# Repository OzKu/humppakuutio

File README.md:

# Humppakuutio - the experience
This is git for our awesome project!

## Parts
- BlueGiga WT32-i (A2DP audiomodule)
- Arduino xyz
- Touchscreen with or without mSD shield
- Opamps for differential audio
- D-Class amplifier
	- Lepai LP-2020A+
- 6x9" car elements
- Some battery
	- LiPo?
	- Lead-acid(12V 7.2Ah)?
	- NiMh?
- Case

## Resources/links

## Idea behind intromenuetc
So I started making introscreen that shows when device is powered up, but nothing is playing.
When it gets streaming is started, it changes to playmenu (own function now).
When phone is disconnected, it changes back to introscreen.

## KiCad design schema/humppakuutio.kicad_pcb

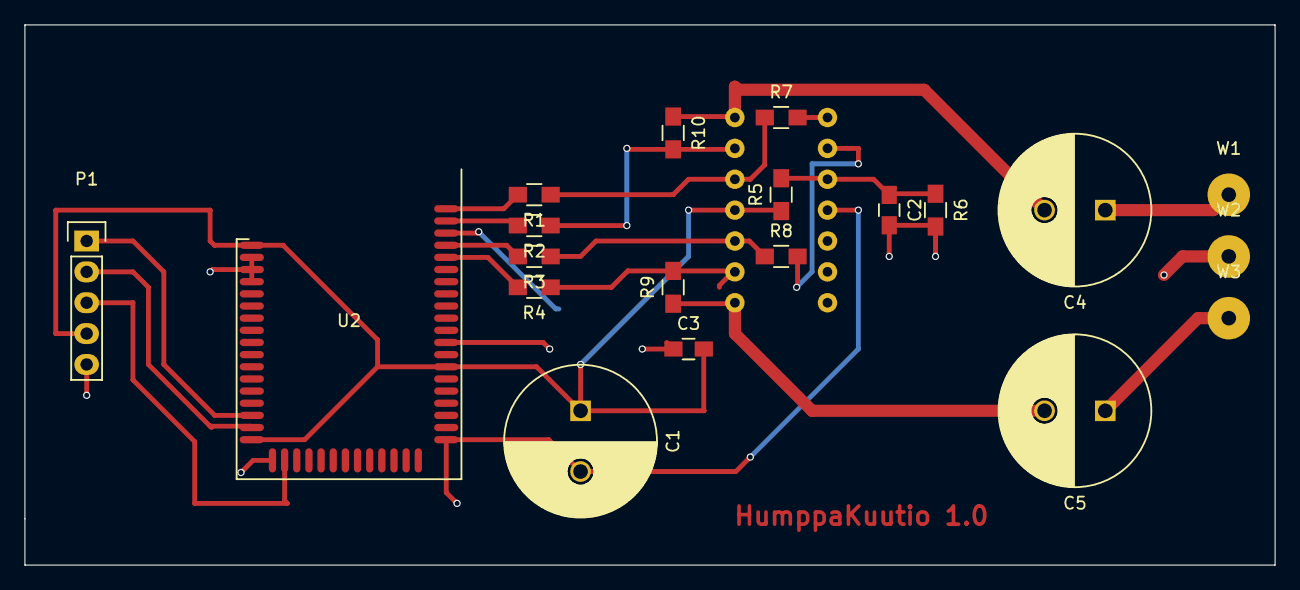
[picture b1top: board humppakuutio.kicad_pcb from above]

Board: 2 copper layers, 102.9 x 44.4 mm, 21 parts (1 on the bottom side), 20 nets.

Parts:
C1, C4, C5: 470u; C_Radial_D12.5_L25_P5
C2, C3: 2u2; C_0805_HandSoldering
P1: CONN_01X05; Pin_Header_Straight_1x05
R1, R2, R3, R4, R5, R6, R7, R8, R9, R10: 10k 0.1%; R_0805_HandSoldering
U1: TL074; DIP-14_W7.62mm
U2: WT32
W1: LEFT; SolderWirePad_single_1-2mmDrill
W2: GNDA; SolderWirePad_single_1-2mmDrill
W3: RIGHT; SolderWirePad_single_1-2mmDrill

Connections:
GNDA: C2.2, C3.1, R6.2, U2.39, U2.43, U2.48, W2.1
GNDD: C1.2, P1.5, U1.11, U2.2, U2.3, U2.4, U2.18, U2.31
unnamed: C2.1, R5.2, R6.1, U1.10
unnamed: C4.1, W1.1
unnamed: C4.2, R10.1, U1.7
unnamed: C5.1, W3.1
unnamed: C5.2, R9.1, U1.1
unnamed: P1.1, U2.15
unnamed: P1.2, U2.16
unnamed: P1.3, U2.19
unnamed: R1.1, R7.1, U1.5
unnamed: R1.2, U2.50
unnamed: R2.2, U2.49
unnamed: R3.1, R8.1, U1.3
unnamed: R3.2, U2.47
unnamed: R4.1, R9.2, U1.2
unnamed: R4.2, U2.46
unnamed: R2.1, R10.2, U1.6
VCC: C1.1, C3.2, P1.4, R5.1, U1.4, U2.1, U2.17, U2.37
VCOM: R7.2, R8.2, U1.8, U1.9

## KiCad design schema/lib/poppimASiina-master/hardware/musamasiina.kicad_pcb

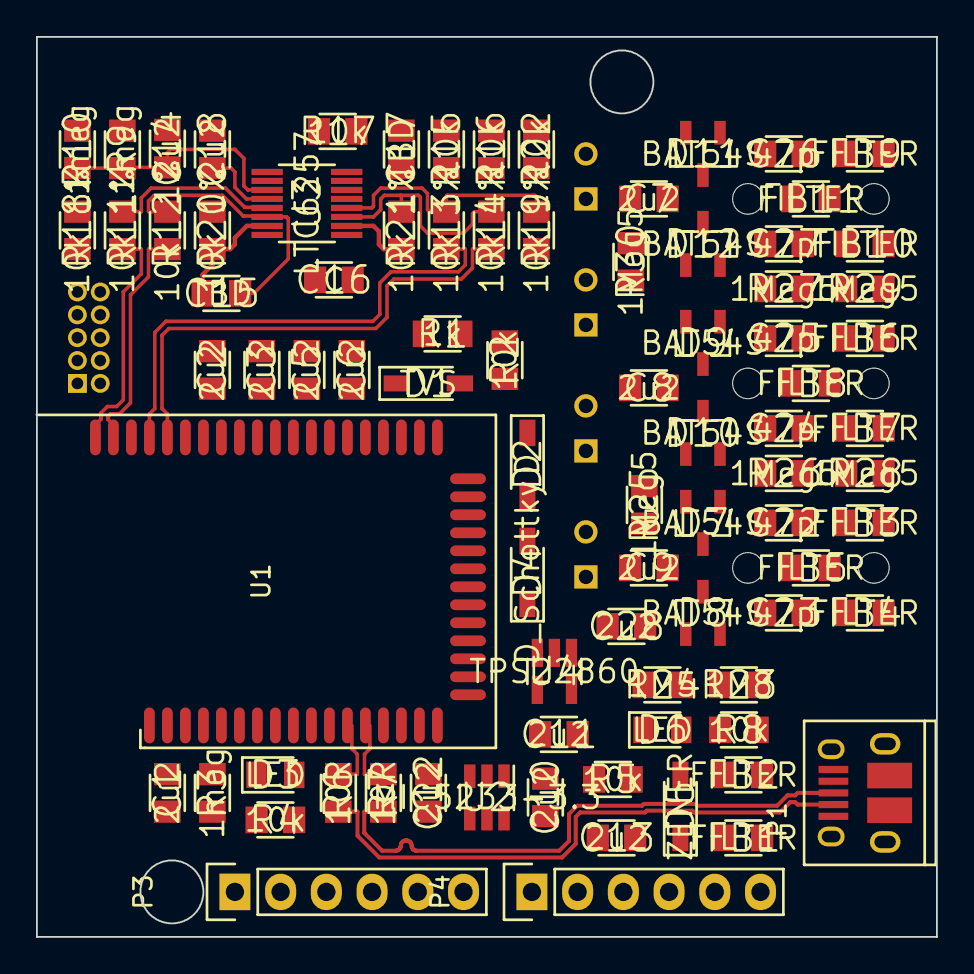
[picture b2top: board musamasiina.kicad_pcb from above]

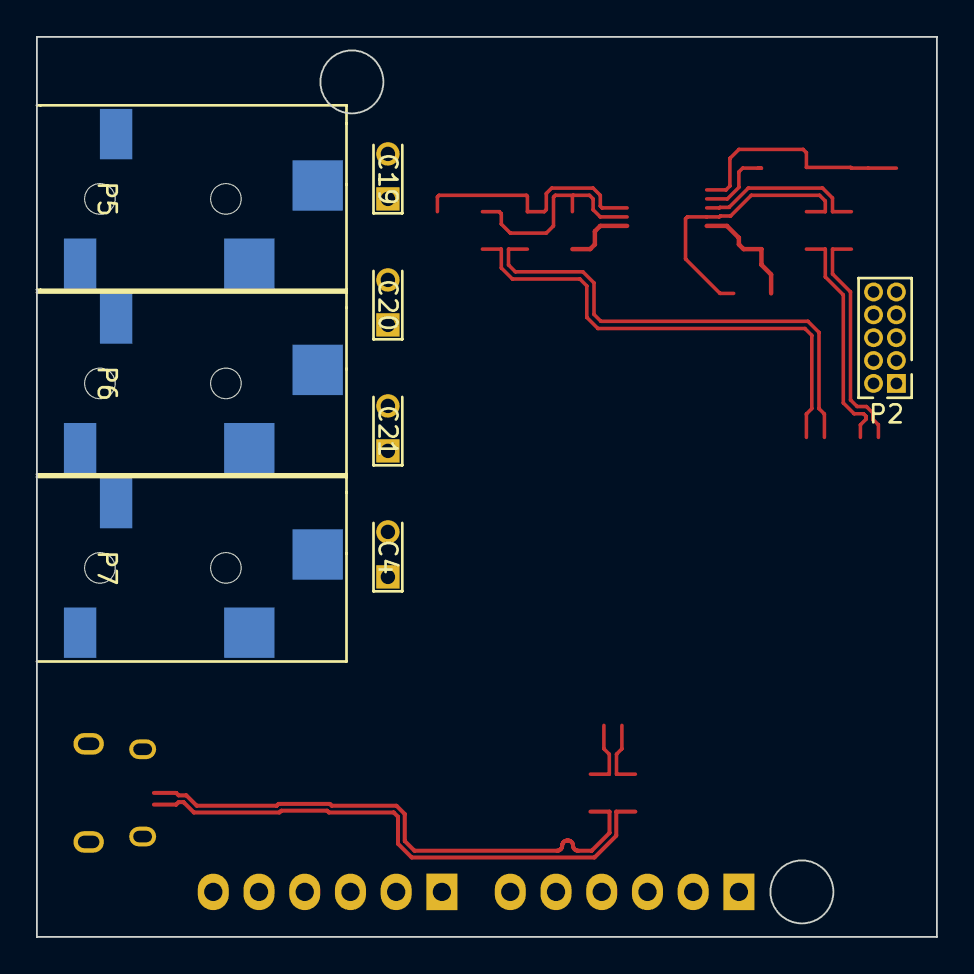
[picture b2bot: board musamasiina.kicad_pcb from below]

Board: 2 copper layers, 50.0 x 50.0 mm, 92 parts (8 on the bottom side), 68 nets.

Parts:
C1, C2, C3, C5, C6, C7, C8, C9, C10, C11, C12, C13, C14, C18, C28: 2u2; SMD0805-CAP-M
C4: AFK477M10F24T-F; C_Radial_D6.3_L13_P2-5_Bent
C15, C17: TBD; SMD0805-CAP-M
C16: C; SMD0805-CAP-M
C19, C20, C21: 470u; C_Radial_D6.3_L13_P2-5_Bent
C22, C23, C24, C25, C26, C27: 47p; SMD0805-CAP-M
D1: TVS; SOD323-M
D2: D; SOD323-M
D3, D6: LED; SMD0805-LED-M
D4: D_Schottky; SOD323-M
D5: ZENER; SOD323-M
D7, D8, D9, D10, D11, D12: BAT54S; SOT23-M
FB1, FB2, FB3, FB4, FB5, FB6, FB7, FB8, FB9, FB10, FB11: FILTER; SMD0805-FERRITE-M
P1: USB_OTG; USB_Micro-B_10103594-0001LF
P2: CONN_02X05; Pin_Header_Straight_2x05_Pitch1.27mm
P3: CONN_02X03; Pin_Header_Straight_1x06
P4: CONN_01X06; Pin_Header_Straight_1x06
P5, P6, P7: CONN_01X03; SMD_3-5mm_jack_CUI-SJ-352X-SMT
R1: 1k; SMD0805-RES-M
R2, R4, R5, R8, R15, R16, R17, R22: 10k; SMD0805-RES-M
R3, R9, R10: 1meg; SMD0805-RES-M
R6, R7: 10R; SMD0805-RES-M
R11, R12, R13, R14, R18, R19, R20, R21: 10k 1%; SMD0805-RES-M
R23: 1M8; SMD0805-RES-M
R24: 1M5; SMD0805-RES-M
R25, R26, R27, R28, R29, R30: 1Meg5; SMD0805-RES-M
U1: WT32
U2: MIC5233-3.3; SOT23-6-M
U3: LTC6257; MSOP16-05mm-M
U4: TPS22860; SOT23-5-M

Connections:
+5V: C10.1, C13.1, D4.1, D5.1, FB1.2, R8.1, U2.1
+BATT: C4.1, C11.1, D1.1, D4.2, U1.37, U4.4, U4.5
/Analog/LEFT_OPAMP+: R11.1, R18.1, U3.5
/Analog/LEFT_OPAMP-: C15.2, R12.1, R20.2, U3.6
/Analog/LEFT_SE: C15.1, C19.2, R15.2, R20.1, U3.7
/Analog/LO_N: R12.2, U1.49
/Analog/LO_P: R11.2, U1.50
/Analog/RIGHT_OPAMP+: R13.1, R19.1, U3.12
/Analog/RIGHT_OPAMP-: C16.2, R14.1, R21.2, U3.11
/Analog/RIGHT_SE: C16.1, C20.2, R16.2, R21.1, U3.10
/Analog/RO_N: R14.2, U1.46
/Analog/RO_P: R13.2, U1.47
/CD+: R7.1, U1.12
/CD-: R6.1, U1.11
/IN_LEFT: C5.2, U1.44
/IN_RIGHT: C6.2, U1.41
/Line in/ESD+: C9.1, D7.2, D8.2, R23.2, R24.1
/Line in/GROUND_CABLE: FB5.2, P7.2
/Line in/LEFT_CABLE: FB3.2, P7.1
/Line in/LEFT_DEVICE: C5.1, C22.1, D7.3, FB3.1, R26.1
/Line in/RIGHT_CABLE: FB4.2, P7.3
/Line in/RIGHT_DEVICE: C6.1, C23.1, D8.3, FB4.1, R25.1
/MISO: P3.1, U1.34
/MOSI: P3.4, U1.35
/MUTE: P2.7, U1.14
/Mono out/GROUND_CABLE: FB8.2, P6.2
/Mono out/LEFT_CABLE: FB6.2, P6.1
/Mono out/LEFT_DEVICE: C21.1, C24.1, C25.1, D9.3, D10.3, FB6.1, FB7.1, R27.1, R28.1
/Mono out/RIGHT_CABLE: FB7.2, P6.3
/NEXT: P2.4, U1.24
/PAUSE: P2.6, U1.22
/PLAY: P2.8, U1.13
/PREV: P2.2, U1.25
/Power Supply/CHRG: D6.1, U1.36
/Power Supply/ENABLE: D2.1, R2.2, U2.3
/Power Supply/GNDBUS: FB2.1, P1.4, P1.5
/Power Supply/VBUS: FB1.1, P1.1
/RESET: P3.5, U1.19
/RXD: P4.4, R5.1, U1.15
/SCLK: P3.3, U1.33
/STOP: P2.9, U1.23
/Stereo out/GROUND_CABLE: FB11.2, P5.2
/Stereo out/LEFT_CABLE: FB9.2, P5.1
/Stereo out/LEFT_DEVICE: C19.1, C26.1, D11.3, FB9.1, R30.1
/Stereo out/RIGHT_CABLE: FB10.2, P5.3
/Stereo out/RIGHT_DEVICE: C20.1, C27.1, D12.3, FB10.1, R29.1
/TXD: P4.5, U1.16
/USB_D+: P1.3, R7.2
/USB_D-: P1.2, R6.2
/VOL+: P2.5, U1.26
/VOL-: P2.3, U1.10
GNDA: C2.1, C3.1, C7.2, C8.2, C9.2, C14.2, C18.1, C22.2, C23.2, C24.2, C25.2, C26.2, C27.2, C28.2, D7.1, D8.1, D9.1, D10.1, D11.1, D12.1, FB5.1, FB8.1, FB11.1, R10.2, R25.2, R26.2, R27.2, R28.2, R29.2, R30.2, U1.39, U1.43, U1.48, U3.13, U4.2
GNDD: C1.2, C4.2, C10.2, C11.2, C12.2, C13.2, D5.2, FB2.2, P2.10, P3.6, P4.1, R3.2, R4.2, R24.2, U1.2, U1.3, U1.4, U1.18, U1.31, U2.2
unnamed: C1.1, D2.2, R1.1, U1.1
unnamed: C2.2, U1.45
unnamed: C3.2, U1.42
unnamed: C14.1, R9.2, R10.1, U3.3
unnamed: C17.1, C21.2, R22.1, U3.16
unnamed: C17.2, R17.1, R22.2, U3.15
unnamed: D1.2, R1.2
unnamed: D3.1, R4.1
unnamed: D3.2, R2.1, R3.1, U1.7
unnamed: D6.2, R8.2
unnamed: R15.1, R16.1, U3.14
unnamed: U1.20, U1.21
VAA: C7.1, C8.1, C18.2, C28.1, D9.2, D10.2, D11.2, D12.2, R9.1, U3.4, U4.1
VCOM: R17.2, R18.2, R19.2, U3.1, U3.2
VDD: C12.1, P2.1, P3.2, P4.3, R5.2, R23.1, U1.17, U2.5

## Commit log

2016-10-06 Initial readme
2016-10-13 Kaunis PoC
2016-10-13 Add button icons
2016-10-13 Add fancy touch effect
2016-10-20 added documentation for BT
2016-10-20 Changed directory structure, added iWrap library files and example
2016-10-20 Changed main.ino to humppakuutio.ino
2016-10-20 Add scrolling text class
2016-10-20 Updated libraries and added iWrap5 guide
2016-10-20 Changed iWrap name
2016-10-21 One-way bluetooth communication
2016-11-17 It works
2016-11-22 Fixed filenames, added gitignore, added libraries
    Fixed filenames when using linux CASE does matter.
    Added .gitignore to ignore buildfiles (using atom arduino-upload)
    Added new folder called libraries where every used library is located, so you can just copy those into arduino-libraries
2016-11-22 Made introscreen, changed many things to own functions
2016-11-22 Changes to playpausebutton
2016-11-22 Added working setup menu
    Made fully functional setup menu with those four default buttons, same as in demo. To acces it, in PLAY screen, you'll have to click on right top corner, on INTRO screen, it's in O.
2016-11-24 Send commands every 5 second
2016-11-28 Font fix
2016-11-28 Use scrolling text for title and artist
2016-11-28 Do not scroll short text
2016-11-29 Refactoring, use platform io
2016-11-29 Refactoring (unfinished)
2016-11-29 Refactoring continued
2016-11-29 Rename colors file
2016-11-29 Move connection management logic into a separate class
2016-11-29 Stop using pragma once, move SimpleTimer into lib folder
2016-12-05 First attempt to make hw
2016-12-05 Hardware, attempt 2
2016-12-07 HW ready for making
2016-12-07 mirrored
2016-12-17 Arduino Mega Shield 0.1
